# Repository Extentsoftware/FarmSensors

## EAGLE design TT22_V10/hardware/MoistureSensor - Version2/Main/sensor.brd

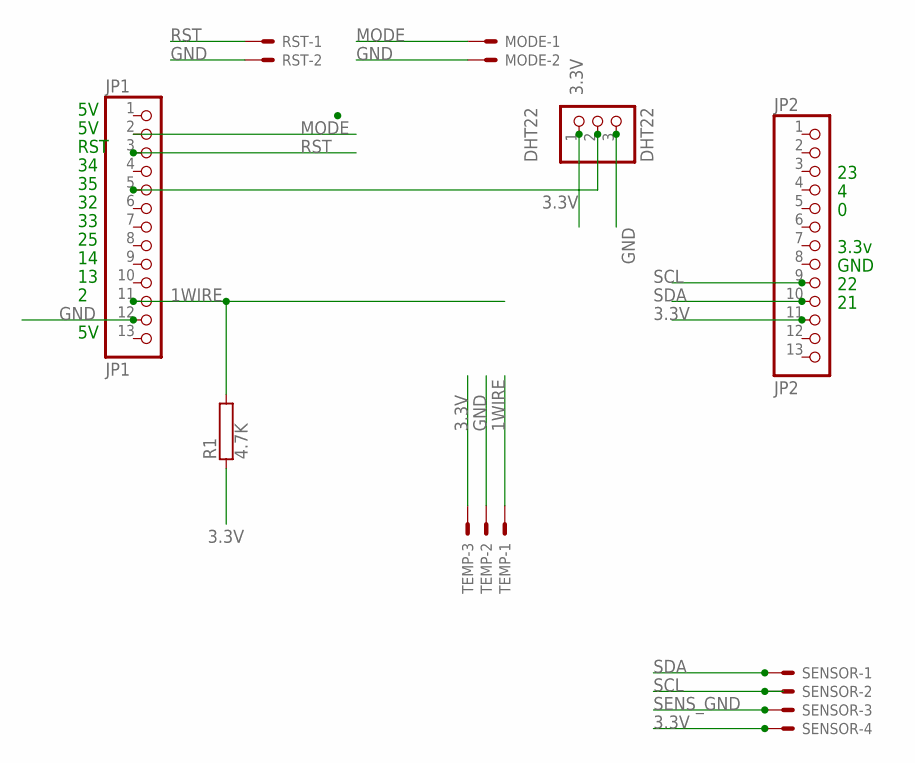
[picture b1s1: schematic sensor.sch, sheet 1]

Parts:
DHT22: DHT22; 1X03
JP1: JP1; 1X13
JP2: JP2; 1X13
MODE: JST-XH-02-PIN-LONG-PAD; JST-XH-02-PACKAGE-LONG-PAD
R1: 4.7K; HPS58
RST: JST-XH-02-PIN-LONG-PAD; JST-XH-02-PACKAGE-LONG-PAD
SENSOR: JST-XH-04-PIN-LONG-PAD; JST-XH-04-PACKAGE-LONG-PAD
TEMP: JST-XH-03-PIN-LONG-PAD; JST-XH-03-PACKAGE-LONG-PAD

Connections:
1WIRE: JP1.11, R1.2, TEMP.1
3.3V: DHT22.1, JP2.11, R1.1, SENSOR.4, TEMP.3
GND: DHT22.3, JP1.12, MODE.2, RST.2, TEMP.2
MODE: JP1.2, MODE.1
unnamed: DHT22.2, JP1.5
RST: JP1.3, RST.1
SCL: JP2.9, SENSOR.2
SDA: JP2.10, SENSOR.1
SENS_GND: SENSOR.3

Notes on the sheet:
RST
GND
3.3v

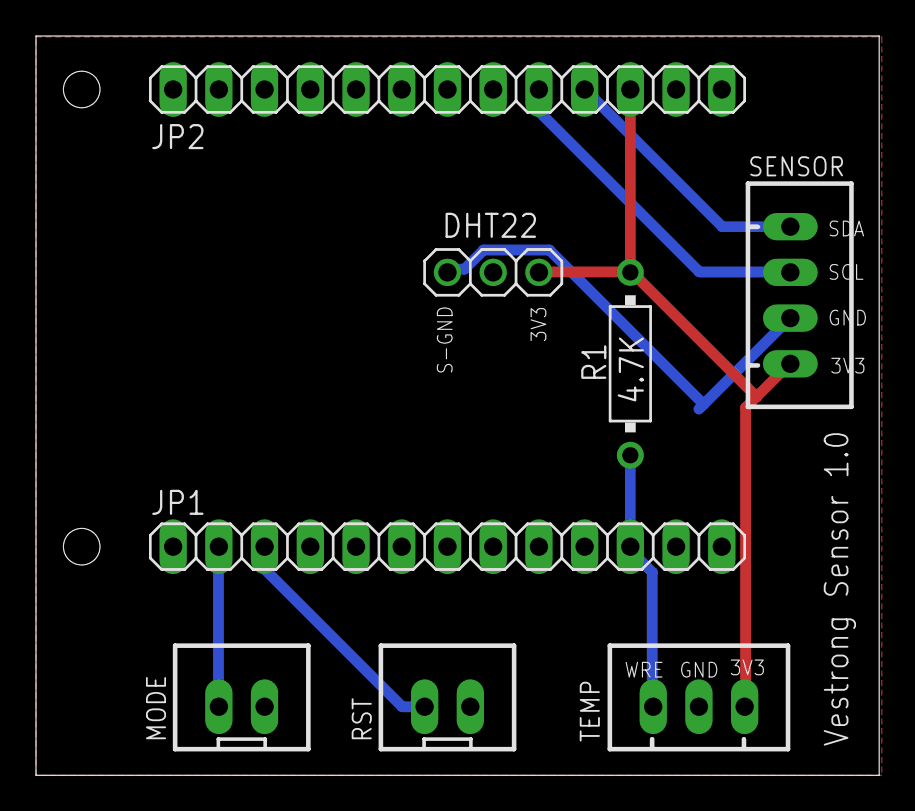
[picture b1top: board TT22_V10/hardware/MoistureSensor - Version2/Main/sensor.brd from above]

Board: 2 copper layers, 46.8 x 41.1 mm, 8 parts (0 on the bottom side), 8 nets.

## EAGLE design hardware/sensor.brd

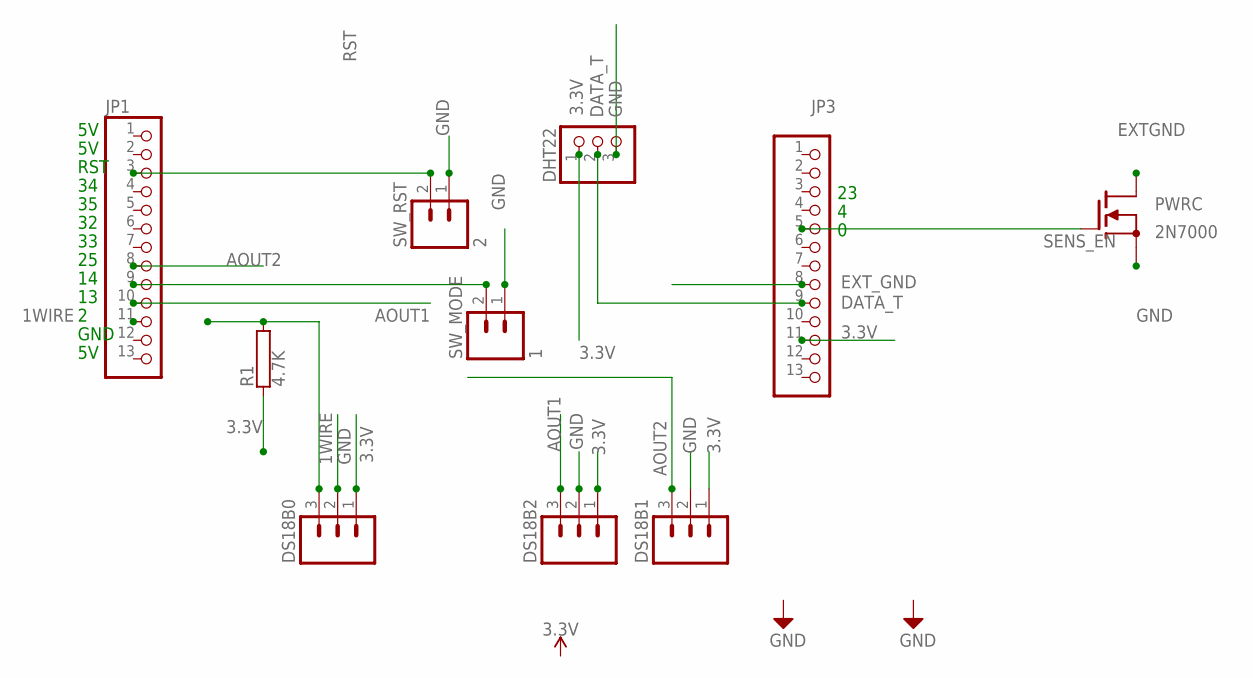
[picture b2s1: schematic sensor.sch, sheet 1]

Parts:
DHT22: PINHD-1X3; 1X03
DS18B0, DS18B1, DS18B2: M03; 03P
JP1, JP3: PINHD-1X13; 1X13
PWRC: 2N7000; TO92
R1: 4.7K; AC01
SW_MODE: 1; 02P
SW_RST: 2; 02P

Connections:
1WIRE: DS18B0.3, JP1.11, R1.2
3.3V: DHT22.1, DS18B0.1, DS18B1.1, DS18B2.1, JP3.11, R1.1
AOUT1: DS18B2.3, JP1.10
AOUT2: DS18B1.3, JP1.8
DATA_T: DHT22.2, JP3.9
EXTGND: PWRC.E (D)
EXT_GND: JP3.8
GND: DHT22.3, DS18B0.2, DS18B1.2, DS18B2.2, PWRC.C (S), SW_MODE.1, SW_RST.1
MODE: JP1.9, SW_MODE.2
RST: JP1.3, SW_RST.2
SENS_EN: JP3.5, PWRC.B (G)

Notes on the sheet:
GND
RST

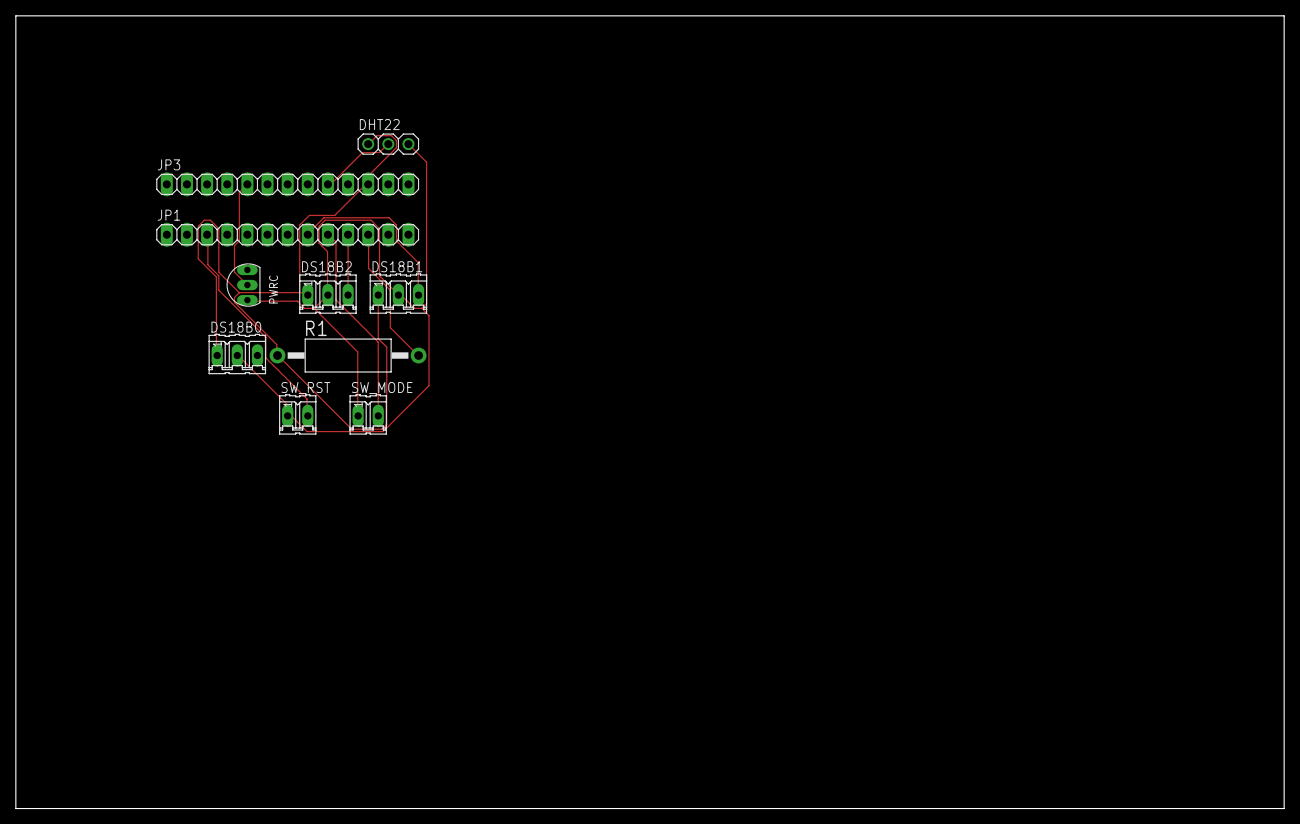
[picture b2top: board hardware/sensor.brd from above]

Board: 2 copper layers, 160.0 x 100.0 mm, 10 parts (0 on the bottom side), 9 nets.

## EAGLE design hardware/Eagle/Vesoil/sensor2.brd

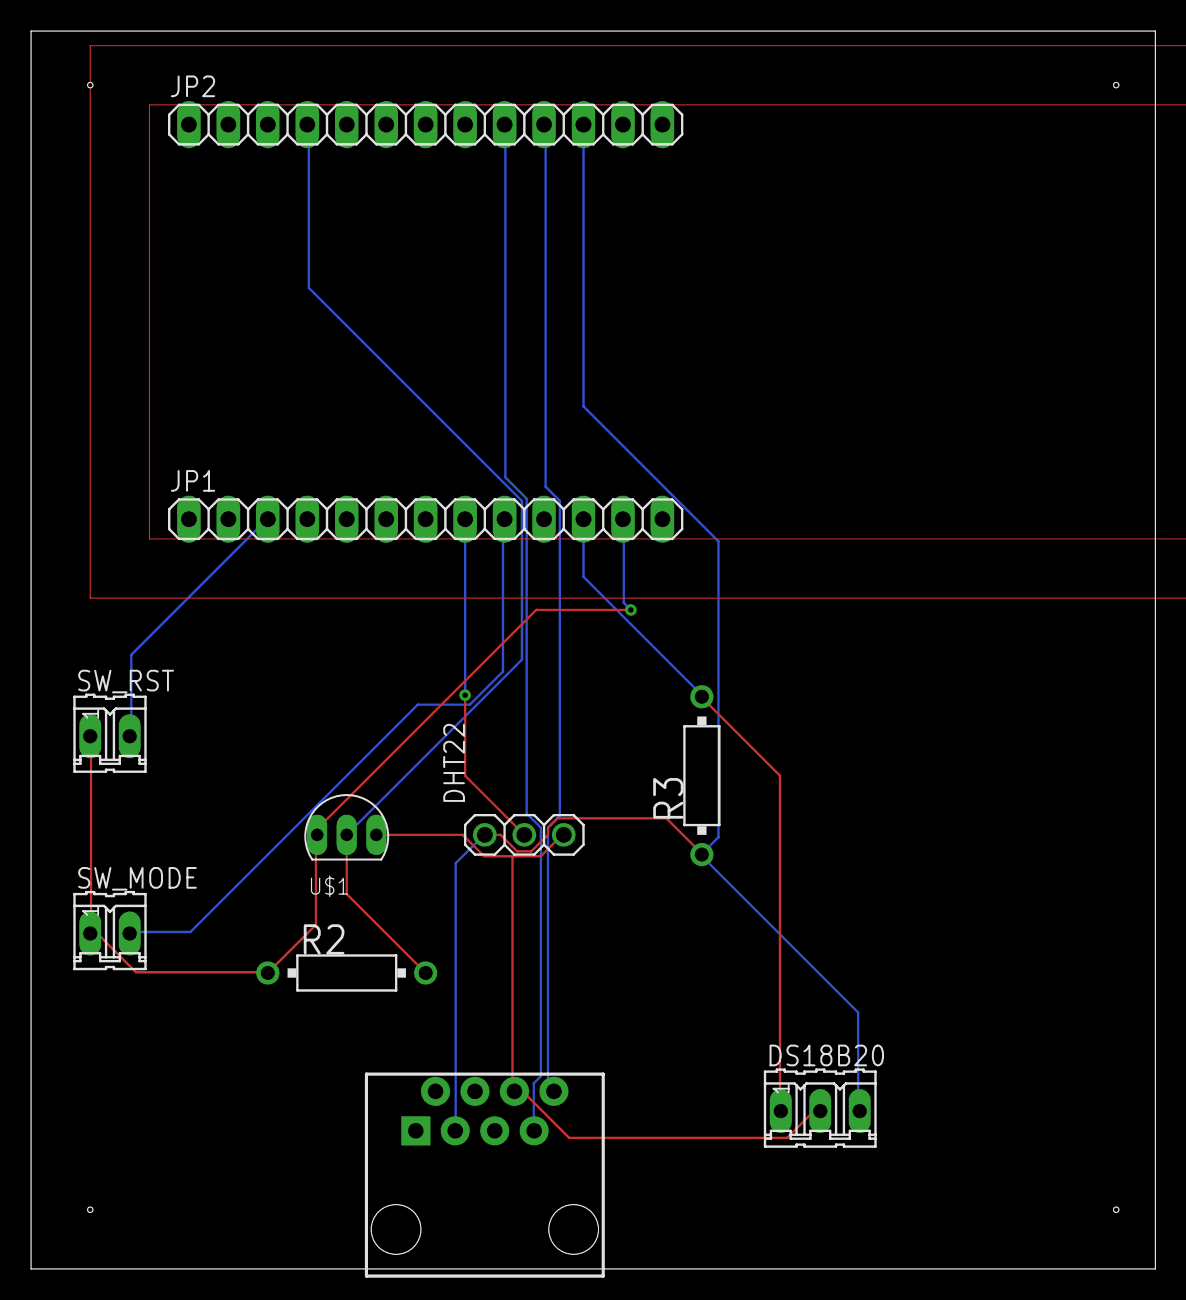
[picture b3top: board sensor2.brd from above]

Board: 2 copper layers, 72.4 x 79.7 mm, 10 parts (0 on the bottom side), 10 nets.

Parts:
DHT22: DHT22; 1X03
DS18B20: DS18B20; 03P
J1: RJ45; RJ45-8
JP1: JP1; 1X13
JP2: JP2; 1X13
R2: 2K; HPS58
R3: 4.7K; HPS58
SW_MODE: SW1; 02P
SW_RST: SW2; 02P
U$1: 2N7000; TO92

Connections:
1WIRE: DS18B20.1, JP1.11, R3.2
3.3V: DHT22.1, DS18B20.3, J1.3, JP2.11, R3.1
DATA_T: DHT22.2, JP1.8
GND: JP1.12, R2.1, SW_MODE.1, SW_RST.1, U$1.C
MODE: JP1.9, SW_MODE.2
unnamed: JP2.4, R2.2, U$1.B
RST: JP1.3, SW_RST.2
SCL: J1.7, JP2.9
SDA: J1.8, JP2.10
SENS_GND: DHT22.3, DS18B20.2, J1.6, U$1.E

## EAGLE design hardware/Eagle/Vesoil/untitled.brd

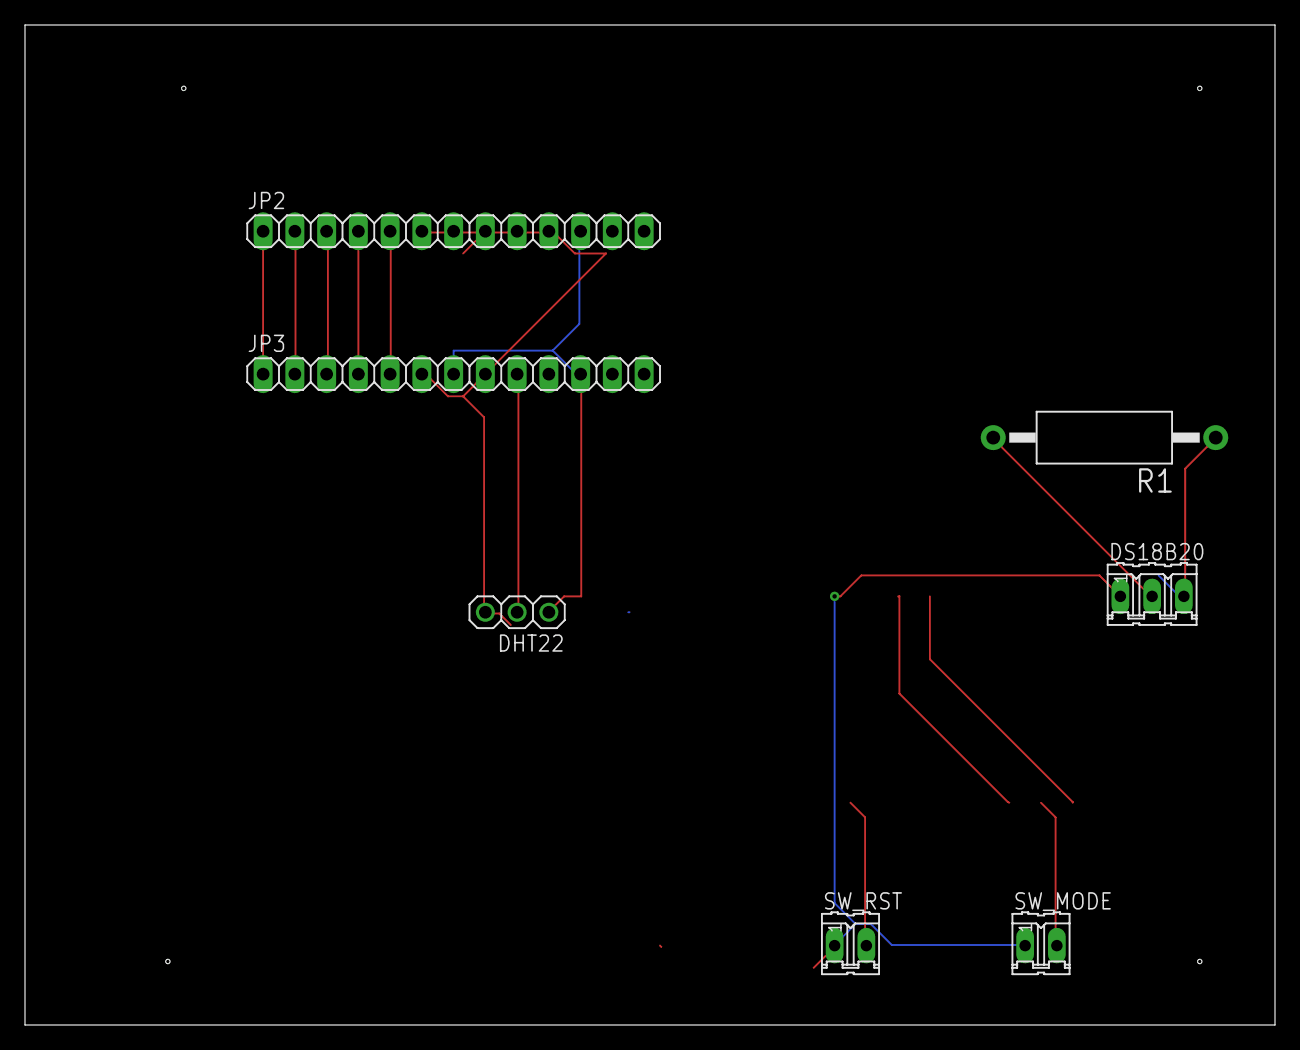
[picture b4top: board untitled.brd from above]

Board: 2 copper layers, 100.0 x 80.0 mm, 7 parts (0 on the bottom side), 11 nets.

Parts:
DHT22: 1X03
DS18B20: 03P
JP2, JP3: 1X13
R1: 4.7K; AC01
SW_MODE: 02P
SW_RST: 02P

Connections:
1WIRE: DS18B20.2, R1.2
3.3V: DHT22.1, JP2.11, JP3.7, JP3.11
DATA_T: DHT22.2, JP3.9
GND: DS18B20.1, SW_MODE.1, SW_RST.1
unnamed: JP2.1, JP3.1
unnamed: JP2.2, JP3.2
unnamed: JP2.3, JP3.3
unnamed: JP2.4, JP3.4
PGM: JP2.5, JP3.5
S$2: DS18B20.3, R1.1
S$6: DHT22.3, JP2.6, JP2.8, JP3.6, JP3.8

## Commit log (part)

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2019-07-03 initial
2019-07-03 started readme
2019-07-04 preferences
2019-07-05 sensor work
2019-07-06 tiny gps work
2019-07-06 fixed build
2019-07-10 sensor
2019-07-10 moved to platformio
2019-07-10 more platform.io work
2019-07-10 platform work
2019-07-10 added library
2019-07-11 change startup modes
2019-07-11 new modes
2019-07-11 typos
2019-07-11 docs
2019-07-12 updated docs
2019-07-12 readme
2019-07-21 library dependencies
2019-07-21 start on sensor UI
2019-07-21 fix radio xmit
2019-07-21 complete web form config
2019-07-21 send diagnostics
2019-07-22 startup modes for hub
2019-07-22 included power settings
2019-07-23 board changes
2019-07-23 fixed defaults
2019-07-25 rearranged lora startup
2019-07-27 testbed
2019-07-28 working 125khz, sf6/cr5
2019-07-28 migrated radio settings to main project
2019-07-28 Adjusted power settings
2019-08-01 hardware changes
2019-08-01 debug
2019-08-02 changed to 15min broadcast
2019-08-05 changed modes on hub
2019-08-06 implemented wifi toggle
2019-08-07 tidyup
2019-08-10 move pwr to gpio4
2019-08-11 sensor changes
2019-08-13 startup changes
2019-08-13 beast 2 setup
2019-08-15 move to i2c
2019-08-16 i2c work
2019-08-21 biard
2019-08-22 wake up time issues
2019-08-30 set correct delay for temp sensor
2019-09-10 reorganise for two TTGO board types
2019-09-10 axp changes
2019-09-11 axp192 work
2019-09-11 power library
2019-09-11 fixed gps wakeup
2019-09-12 power experiments
2019-09-13 gitignore
2019-09-13 power changes
2019-09-13 introduce power into v10 hub
2019-09-13 power changes to the hub
2019-09-13 updated readne
2019-09-15 removed redundant files
2019-09-20 hub version and gps diagnostics
2019-09-24 cleanup
2019-10-13 power mode
2019-10-13 hub wifi timeout
2020-02-25 update libs
2020-03-27 capability
2020-04-25 fix sensors
2020-05-16 Delays
2020-07-08 display changes
2020-07-10 mqtt work
2020-07-16 reorg boards
2020-07-23 add wifi
2020-08-31 added ds18b20
2020-11-20 reconfigure
2020-11-21 header working
2020-11-26 onewire work
2020-12-21 new at85ADC
2020-12-22 added oscillator
2020-12-24 generic adc + frequency counter
2020-12-24 message
2021-01-11 sensor board work
2021-02-21 drill
2021-04-10 new board
2021-04-20 fix hub
2021-04-23 mods
2021-04-26 implement wifi mode
2021-04-28 include dallas
2021-04-28 add dallas
2021-05-15 design changes
2021-05-16 pcb changes
2021-05-18 drill hole changes
2021-06-19 organise folders
2021-06-19 Bump lodash
    Bumps [lodash](https://github.com/lodash/lodash) from 4.17.11 to 4.17.21.
    - [Release notes](https://github.com/lodash/lodash/releases)
    - [Commits](https://github.com/lodash/lodash/compare/4.17.11...4.17.21)
    ---
    updated-dependencies:
    - dependency-name: lodash
2021-06-19 Bump y18n
    Bumps [y18n](https://github.com/yargs/y18n) from 3.2.1 to 3.2.2.
    - [Release notes](https://github.com/yargs/y18n/releases)
    - [Changelog](https://github.com/yargs/y18n/blob/master/CHANGELOG.md)
    - [Commits](https://github.com/yargs/y18n/commits)
    ---
    updated-dependencies:
2021-06-19 Bump hosted-git-info
    Bumps [hosted-git-info](https://github.com/npm/hosted-git-info) from 2.7.1 to 2.8.9.
    - [Release notes](https://github.com/npm/hosted-git-info/releases)
    - [Changelog](https://github.com/npm/hosted-git-info/blob/v2.8.9/CHANGELOG.md)
    - [Commits](https://github.com/npm/hosted-git-info/compare/v2.7.1...v2.8.9)
    ---
    updated-dependencies:
2021-06-19 Bump handlebars
    Bumps [handlebars](https://github.com/wycats/handlebars.js) from 4.0.12 to 4.7.7.
    - [Release notes](https://github.com/wycats/handlebars.js/releases)
    - [Changelog](https://github.com/handlebars-lang/handlebars.js/blob/master/release-notes.md)
    - [Commits](https://github.com/wycats/handlebars.js/compare/v4.0.12...v4.7.7)
    ---
    updated-dependencies:
2021-06-19 Bump ws
    Bumps [ws](https://github.com/websockets/ws) from 5.2.2 to 5.2.3.
    - [Release notes](https://github.com/websockets/ws/releases)
    - [Commits](https://github.com/websockets/ws/compare/5.2.2...5.2.3)
    ---
    updated-dependencies:
    - dependency-name: ws
2021-06-19 remove old dirs
2021-06-19 Bump lodash in /src/server/docker/grafana/plugins/grafana-worldmap-panel
    Bumps [lodash](https://github.com/lodash/lodash) from 4.17.11 to 4.17.21.
    - [Release notes](https://github.com/lodash/lodash/releases)
    - [Commits](https://github.com/lodash/lodash/compare/4.17.11...4.17.21)
    ---
    updated-dependencies:
    - dependency-name: lodash
2021-06-19 Bump ws in /src/server/docker/grafana/plugins/grafana-worldmap-panel
    Bumps [ws](https://github.com/websockets/ws) from 5.2.2 to 5.2.3.
    - [Release notes](https://github.com/websockets/ws/releases)
    - [Commits](https://github.com/websockets/ws/compare/5.2.2...5.2.3)
    ---
    updated-dependencies:
    - dependency-name: ws
2021-06-19 Bump y18n in /src/server/docker/grafana/plugins/grafana-worldmap-panel
    Bumps [y18n](https://github.com/yargs/y18n) from 3.2.1 to 3.2.2.
    - [Release notes](https://github.com/yargs/y18n/releases)
    - [Changelog](https://github.com/yargs/y18n/blob/master/CHANGELOG.md)
    - [Commits](https://github.com/yargs/y18n/commits)
    ---
    updated-dependencies:
2021-06-19 more updates
2021-08-05 Bump tar in /src/server/docker/grafana/plugins/grafana-worldmap-panel
    Bumps [tar](https://github.com/npm/node-tar) from 4.4.8 to 4.4.15.
    - [Release notes](https://github.com/npm/node-tar/releases)
    - [Changelog](https://github.com/npm/node-tar/blob/main/CHANGELOG.md)
    - [Commits](https://github.com/npm/node-tar/compare/v4.4.8...v4.4.15)
    ---
    updated-dependencies:
2021-08-13 Bump path-parse
    Bumps [path-parse](https://github.com/jbgutierrez/path-parse) from 1.0.6 to 1.0.7.
    - [Release notes](https://github.com/jbgutierrez/path-parse/releases)
    - [Commits](https://github.com/jbgutierrez/path-parse/commits/v1.0.7)
    ---
    updated-dependencies:
    - dependency-name: path-parse
2021-08-15 change constants
2021-08-25 fixes for 1wire
2021-09-01 noise cancelling mode
2021-09-01 Low noise updates
2021-09-01 reliability updates
2021-09-02 Bump tar in /src/server/docker/grafana/plugins/grafana-worldmap-panel
    Bumps [tar](https://github.com/npm/node-tar) from 4.4.8 to 4.4.19.
    - [Release notes](https://github.com/npm/node-tar/releases)
    - [Changelog](https://github.com/npm/node-tar/blob/main/CHANGELOG.md)
    - [Commits](https://github.com/npm/node-tar/compare/v4.4.8...v4.4.19)
    ---
    updated-dependencies:
2021-09-14 added locatin and distance
2021-09-14 updates for geohash
2021-09-22 Bump tmpl in /src/server/docker/grafana/plugins/grafana-worldmap-panel
    Bumps [tmpl](https://github.com/daaku/nodejs-tmpl) from 1.0.4 to 1.0.5.
    - [Release notes](https://github.com/daaku/nodejs-tmpl/releases)
    - [Commits](https://github.com/daaku/nodejs-tmpl/commits/v1.0.5)
    ---
    updated-dependencies:
    - dependency-name: tmpl
2021-10-16 latest changes
2021-10-16 print id
2021-10-19 rework Hub
2021-10-24 minor changes
2021-11-01 fix sensor id
2021-12-08 changes for econet
2021-12-14 gps changes
2021-12-15 update dashboard
2021-12-17 improve message handling
2021-12-25 updates to hub
2021-12-25 sim changes
2021-12-26 fixes
2021-12-29 updtes
2022-01-04 library updates
2022-01-05 fixes for reliability
2022-01-17 resilience changes
2022-02-13 Bump ajv in /src/server/docker/grafana/plugins/grafana-worldmap-panel
    Bumps [ajv](https://github.com/ajv-validator/ajv) from 6.5.5 to 6.12.6.
    - [Release notes](https://github.com/ajv-validator/ajv/releases)
    - [Commits](https://github.com/ajv-validator/ajv/compare/v6.5.5...v6.12.6)
    ---
    updated-dependencies:
    - dependency-name: ajv
2022-04-09 Bump moment in /src/server/docker/grafana/plugins/grafana-worldmap-panel
    Bumps [moment](https://github.com/moment/moment) from 2.22.2 to 2.29.2.
    - [Release notes](https://github.com/moment/moment/releases)
    - [Changelog](https://github.com/moment/moment/blob/develop/CHANGELOG.md)
    - [Commits](https://github.com/moment/moment/compare/2.22.2...2.29.2)
    ---
    updated-dependencies:
2022-04-19 pcb manufacture
2022-04-19 Added repeater
2022-04-21 box for repeater
2022-04-23 added new hub code
2022-04-25 move to TTGO Lora32
2022-04-29 fixes for sim
2022-04-29 Bump async in /src/server/docker/grafana/plugins/grafana-worldmap-panel
    Bumps [async](https://github.com/caolan/async) from 2.6.1 to 2.6.4.
    - [Release notes](https://github.com/caolan/async/releases)
    - [Changelog](https://github.com/caolan/async/blob/v2.6.4/CHANGELOG.md)
    - [Commits](https://github.com/caolan/async/compare/v2.6.1...v2.6.4)
    ---
    updated-dependencies:
2022-05-05 get sim working in Austria
2022-05-07 build too big
2022-05-08 bluetooth
2022-05-08 BLE Server
2022-05-08 client work
2022-05-09 more BLE work
2022-05-11 more work on ble
2022-05-11 more BLE
2022-05-25 radio changes
2022-05-25 Hub updates
2022-05-31 added loraempty
2022-06-18 fix for spi
2022-06-18 test work
2022-06-19 fix connection
2022-06-26 fix lora
2022-07-06 enable bluetooth
2022-07-06 add gps
2022-07-06 updates to status
2022-07-08 Bump moment in /src/server/docker/grafana/plugins/grafana-worldmap-panel
    Bumps [moment](https://github.com/moment/moment) from 2.22.2 to 2.29.4.
    - [Release notes](https://github.com/moment/moment/releases)
    - [Changelog](https://github.com/moment/moment/blob/develop/CHANGELOG.md)
    - [Commits](https://github.com/moment/moment/compare/2.22.2...2.29.4)
    ---
    updated-dependencies:
2022-07-09 updates to gps
2022-11-11 Bump loader-utils
    Bumps [loader-utils](https://github.com/webpack/loader-utils) from 1.1.0 to 1.4.2.
    - [Release notes](https://github.com/webpack/loader-utils/releases)
    - [Changelog](https://github.com/webpack/loader-utils/blob/v1.4.2/CHANGELOG.md)
    - [Commits](https://github.com/webpack/loader-utils/compare/v1.1.0...v1.4.2)
    ---
    updated-dependencies:
2022-11-11 Bump minimatch
    Bumps [minimatch](https://github.com/isaacs/minimatch) from 3.0.4 to 3.1.2.
    - [Release notes](https://github.com/isaacs/minimatch/releases)
    - [Commits](https://github.com/isaacs/minimatch/compare/v3.0.4...v3.1.2)
    ---
    updated-dependencies:
    - dependency-name: minimatch
2022-11-20 comments
2022-11-20 led off
2022-11-20 led changes
2022-12-07 Bump decode-uri-component
    Bumps [decode-uri-component](https://github.com/SamVerschueren/decode-uri-component) from 0.2.0 to 0.2.2.
    - [Release notes](https://github.com/SamVerschueren/decode-uri-component/releases)
    - [Commits](https://github.com/SamVerschueren/decode-uri-component/compare/v0.2.0...v0.2.2)
    ---
    updated-dependencies:
    - dependency-name: decode-uri-component
2022-12-12 Bump qs in /src/server/docker/grafana/plugins/grafana-worldmap-panel
    Bumps [qs](https://github.com/ljharb/qs) from 6.5.2 to 6.5.3.
    - [Release notes](https://github.com/ljharb/qs/releases)
    - [Changelog](https://github.com/ljharb/qs/blob/main/CHANGELOG.md)
    - [Commits](https://github.com/ljharb/qs/compare/v6.5.2...v6.5.3)
    ---
    updated-dependencies:
2023-05-16 try heltec board
2023-05-22 updates to use i2c
2023-05-22 minor update to remove old code
2023-05-23 change display msg
2023-06-05 update msg
2023-08-25 added bme280
2023-08-28 bme280 additions
2023-08-28 additions
2023-08-31 BME280 work
2023-09-05 server changes
2023-09-22 add bme code
2023-10-15 turn off debg
2023-10-16 fix sensor list
2024-03-30 docker updates
2024-04-02 reoganise directories
2024-04-03 change path
2024-04-03 ingree changes
2024-04-05 reorganise directories
2024-04-11 new server
2024-04-17 TTGO Beam + microk8 work
2024-04-17 update SSID
2024-04-17 added missing header
2024-04-17 Remove old passwords
2024-04-17 split bongofn from servers
2024-05-05 update sensor profile
2024-05-05 apply changes
2024-05-06 complete bongofn config
2024-05-07 Upgrade sensor images
2024-05-15 kubernettes updates
2024-05-15 update certificate
2024-05-16 add letsencrypt issuer
2024-06-23 update version
2024-10-07 update library
2024-10-13 fix certificate issuer
2024-10-14 fix file size limits and ingress
2024-12-14 minor fixes
2024-12-22 remove unused file
2025-05-26 update libraries
2025-06-17 add wire setup
2025-10-27 scmitt work
2025-10-28 cubecell updates
2026-03-27 Update farm scout

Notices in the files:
parts and their libraries:
SparkFun-Connectors: Licensing: Creative Commons ShareAlike 4.0 International - https://creativecommons.org/licenses/by-sa/4.0
m-pad-2.1: License : GNU General Public License version 2 (see bottom)
